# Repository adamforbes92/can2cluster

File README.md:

# Can2Cluster

**Get one ready-built:** [Can2Cluster at Forbes Automotive](https://forbes-automotive.com/products/can2cluster?utm_source=github&utm_medium=readme&utm_campaign=can2cluster) · Pair it with a [SpeedPulser](https://forbes-automotive.com/products/speedpulser?utm_source=github&utm_medium=readme&utm_campaign=can2cluster) for cable speedos · Not sure which board you need? See the [speedo, tacho & cluster comparison](https://forbes-automotive.com/collections/speedo-tacho-cluster?utm_source=github&utm_medium=readme&utm_campaign=can2cluster).
Can2Cluster takes CAN messages and turns them into the analogue signals older instrument clusters expect: RPM, speed, Engine Management Light (EML), Electronic Pedal Control light (EPC), reverse and a coolant gauge. It is built around VAG CAN messages (PQ and MQB), with Ford, Emerald and Renault ECUs added too, and runs on an ESP32 DevKit board or the newer ESP32-S3 board from the same code.

DSG gearboxes are supported: speed can be worked out from the current gear and RPM, or read over TP2.0 / UDS. The DSG paddle inputs can shift an MQB or PQ gearbox over CAN, or, on a PQ car with an MK4 cruise stalk, the same inputs can carry the cruise stalk to the ECU.

If no speed is available (from hall or CAN), an optional GPS module (like the Neo6M) can provide it, and the speed can be broadcast on CAN for other modules. GPS modules need to see the sky; depending on where the unit is fitted, an external aerial may be needed (standard SMA connector).

Everything is set up from a web page on the unit's own WiFi, so no code editing is needed, and it shows live feedback on what's coming in.

> [!NOTE]
> The pin-out differs between the Version 1 and Version 2 PCBs, although functionality is the same. Confirm pin-outs using the 'Module Pinout' table.

This can be expanded to support other marques and is actively encouraged. Other users are using the DSG support and the EML/EPC outputs for shift lights and other features.

### Purchase
If you want to purchase an assembled Can2Cluster, you can do so here: [Can2Cluster - Forbes Automotive](https://forbes-automotive.com/products/can2cluster)

## Features
| Feature | What it does |
|---|---|
| RPM output | Square wave or high-voltage 'coil type' (MK1/MK2) RPM, from CAN or a hall RPM input |
| Speed output | Square wave speed from hall, VR, ECU, ABS, DSG, TP2.0/UDS, GPS or a custom CAN ID |
| EML / EPC / Reverse | Warning lights and a 5A reverse output from CAN |
| Needle sweep | Sweeps both needles at power-up, as soon as the outputs are ready, up to a settable speedo dial top |
| Shift light | Flashes EML and/or EPC above a set RPM |
| DSG park | Shows Park on the EML or EPC light |
| DSG paddles | Paddle inputs sent to an MQB (0x3DD) or PQ (0x38A) gearbox |
| MK4 cruise stalk | The paddle and hall inputs read an MK4 cruise stalk and send it to a PQ ECU (0x38A) |
| PQ gateway frames | Optional 0x570 / 0x390 / 0x7D0 for a PQ engine and DSG with no gateway |
| Coolant gauge | Drives an MK2-style coolant gauge from the CAN coolant temperature, with a calibration builder |
| GPS + speed broadcast | GPS speed, and any speed put back onto CAN on an ID of your choosing |
| CAN analyzer | Every frame forwarded to SavvyCAN over WiFi or USB |
| OTA updates | Firmware and web page updates from GitHub or from files, no USB needed |

## IO
Can2Cluster uses an 18-pin MX23A18 connector and features the following IO:

#### IO List
| Type | Signal | Notes |
|-----|--------|-------|
| Input | CAN (High & Low) | CANBUS |
| Input | DSG Paddle + / Cruise Main Switch | Ground to activate |
| Input | DSG Paddle - / Cruise SET | Ground to activate |
| Input | Hall Speed / Cruise RESUME | Pull-up/down options |
| Input | Hall RPM | Pull-down ONLY |
| Input | GPS | Neo6M or similar |
| Output | RPM (MK1/MK2) | High voltage 'coil type' |
| Output | RPM Square | Pull-down ONLY |
| Output | Speed Square | Pull-down ONLY |
| Output | EML & EPC | Pull-down ONLY |
| Output | Reverse | 5A high-side |

### Pinout
The MX23A18 connector pinout is:

| Pin | Signal | Notes |
|-----|--------|-------|
| 1 | Vign | 12V Ignition |
| 2 | Ground | Chassis ground |
| 3 | Chassis CAN Low | to Chassis/ECU side |
| 4 | Chassis CAN High | to Chassis/ECU side |
| 5 | Speed | Speed output; pull-down |
| 6 | RPM | RPM output; pull-down |
| 7 | EML | Engine Management Light; pull-down |
| 8 | EPC | Electronic Pedal Control Light; pull-down |
| 9 | Reverse | 12v high-side reverse output; 5A max |
| 10 | Paddle Up / Cruise Main | DSG paddle +, or the MK4 cruise main switch in cruise stalk mode; ground to activate |
| 11 | Paddle Down / Cruise SET | DSG paddle -, or cruise SET in cruise stalk mode; ground to activate |
| 12 | Hall Speed / Cruise RESUME | Hall speed sensor, or cruise RESUME in cruise stalk mode; optional pull-up/down |
| 13 | N/A | Not used |
| 14 | N/A | Not used |
| 15 | N/A | Not used |
| 16 | N/A | Not used (S3 board: coolant gauge output) |
| 17 | N/A | Not used |
| 18 | RPM | High voltage coil pulse; MK1/MK2 etc |

> [!NOTE]
> **Legacy clusters & needle jitter:** on some older clusters the coil-style RPM output can induce a little jitter in the hall inputs due to poor grounding. Fitting a **~500 Ω resistor in series** with the RPM output largely reduces this.

## Setup
Purchased modules come pre-loaded with the most recent firmware; check back here for updates.

1. Connect the module as per the wiring diagram.
2. Power up. WiFi is available straight away and stays on while any client is connected; once the last one disconnects, the radio turns off after 1 minute to save power (see Power Management below).
3. Connect to the device and browse to **192.168.1.1**.
4. Configure the device to suit: needle sweep and dial top, RPM type, speed source, shift light, input mode.
5. Use the **Diagnostics** tab to confirm incoming data.

### WiFi Setup
Connect to the **`Can2Cluster`** access point (open network, no password) and browse to **192.168.1.1** or **c2c.local**. The web page uses Forbes Automotive's shared dark theme, the same look as OpenHaldex, SpeedPulser, SpeedPulserPro, can2rpm, the MQB Steering Wheel Controller and AirLift Controller. Current firmware version: **4.03**.

The web page has five tabs:
- **Dashboard**: final RPM and speed (as numbers or dials) and the status pills.
- **Configuration**: needle sweep, shift light, cluster output (coil RPM, MPH), DSG park, input mode (paddles or MK4 cruise stalk), PQ gateway frames and DSG paddle output.
- **Advanced**: speed broadcast, GPS update rate, CAN analyzer, speed and RPM sources, custom CAN input, DSG speed calculation and the coolant gauge.
- **Diagnostics**: board details, every input side by side, and the output tests.
- **OTA**: updates from GitHub or from files, and Home WiFi (bridge mode).

*Dashboard with the final RPM/speed as dial gauges and the status pills; needle sweep, shift light, cluster output and DSG park on the Configuration tab; speed and RPM source selection under Advanced. Choosing **DSG** as the speed source reveals the gear-ratio calculator (speed = RPM × tyre circumference ÷ gear ratio × final drive).*

**Status indicators:** CAN health, GPS and output (EML/EPC/Reverse) status are shown as coloured pills:

| Colour | Meaning |
|---|---|
| Green | Healthy / active: CAN bus is healthy, GPS has a satellite lock, or the output reflects a real vehicle CAN signal |
| Red | Unhealthy / not available: CAN bus unhealthy, or no GPS module fitted/connected |
| Orange | A caveat, not a failure: GPS module connected but no satellite fix yet ("Connected (no sats)"), or an EML/EPC/Reverse output **forced on by the test/diagnostic mode** rather than a real vehicle signal |

### Needle Sweep
At power-up both needles sweep to the top of the dial and back. The sweep starts as soon as the output pins are set up, a fraction of a second after power-on, and runs on its own while the rest of the unit starts up (GPS search, CAN, WiFi), so there's no wait before it.

**Speedo Dial Top** sets how far the speed needle goes: set it to the highest number on the speedo (60 to 400, km/h or mph to match the cluster). Up to V4.01 the sweep always stopped at 200. **Sweep Speed**, **RPM Step** and **Speed Step** set how long the sweep takes (higher = slower); **Test Needle Sweep** runs one from the page.

## DSG Paddles
Pulling the DSG Paddle +/- inputs puts a paddle request on the CAN bus, whatever the speed source. The **DSG Paddle Output** drop-down picks the frame: **MQB** sends Gateway_74 (`0x3DD`), the frame an MQB gearbox reads its steering-wheel paddles from; **PQ** sends the GRA frame (`0x38A`); **PQ + MQB** sends both; **Off** sends nothing. Pick the one that matches the gearbox: a PQ gearbox only reads `0x38A` and an MQB one only `0x3DD`, so the wrong choice does nothing. Each pull sends **one clean tip**: a short pulse on the paddle's rising edge, then the bit is released, with a brief lock-out before the next shift. That is how the gearbox actually takes a tip (edge-triggered, one shift per press, with a minimum gap between shifts) - worked out by reverse-engineering the DSG firmware, write-ups in [Documents/dsg_re/](Documents/dsg_re/). Holding a paddle gives exactly one shift. If a real gateway is already sending that frame, Can2Cluster stays quiet on it. The MQB gear selector's own frame (`0x0AF`) is only read, never sent: the gearbox checks the lever with a question/answer and a message counter, so it can't be imitated while the real lever is fitted. The card also shows the lever position, the gearbox's tip mode, gear and warning level live, and has **Test Paddle +/-** buttons. The full log analysis is in [MQB_PADDLES.md](MQB_PADDLES.md).

## MK4 Cruise Stalk
For a PQ engine in a car with the MK4 cruise stalk. **Input Mode** (Configuration tab) picks what connector pins 10, 11 and 12 are used for:

| Pin | DSG Paddles (default) | MK4 Cruise Stalk |
|---|---|---|
| 10 | Paddle + | Main switch |
| 11 | Paddle - | SET |
| 12 | Hall speed | RESUME |

In cruise stalk mode each input is on when grounded, and the stalk goes to the ECU in the PQ cruise frame GRA (`0x38A`) every 20 ms: main switch, SET and RESUME, plus "cancel" for a moment when the main switch is switched off. The paddle bits in that frame are always 0, so the stalk can never shift the gearbox, and no paddle frames are sent. Hall speed isn't available in this mode (pin 12 is RESUME), so pick another speed source. The card shows each stalk input and what's being sent live; check every stalk position there before driving. Cruise also has to be enabled in the ECU coding, and the ECU must see both brake switches.

> [!WARNING]
> Match the setting to the wiring. In paddle mode, grounding pin 10 or 11 shifts the gearbox, so never select DSG Paddles while the cruise stalk is wired to those pins. The page asks for confirmation before switching.

**PQ Gateway Frames** (off by default) is for a PQ35/46 engine and DSG in a car without the right gateway. It sends the frames a gateway would normally send, so the ECU and DSG stop logging them as missing: `0x570` (ignition on / engine running and the battery voltage) and `0x390` (reverse gear) every 100 ms, and `0x7D0` every 500 ms with the mileage read from the cluster (`0x520`). Each frame stops by itself while another module sends it, so leave it off on cars that have a gateway.

The cruise stalk and gateway frames were first built by a customer for their own car (an MK4 build of 4.01) and are now part of the standard firmware. Their settings carry across when updating from that build.

## Adding CAN Functionality
Users wishing to add CAN functionality are encouraged to push commits to the project. Incoming CAN messages are handled in `onBodyRX()` (`can2cluster_can.cpp`) and the outputs follow automatically. You'll need to know the CAN ID and bytes you want to process and which variables to put them in.

Two things in the web page help here. **CAN Analyzer** (Advanced tab) forwards every received frame to [SavvyCAN](https://www.savvycan.com/) over WiFi (GVRET, `192.168.1.1:23`) or over the USB serial port, so you can find the ID and bytes you're after. And for a speed signal on a non-standard ID, **Custom CAN Input** (choose *Custom* as the speed source) lets you enter the CAN ID, byte positions, byte order, scale and offset without touching the code:

For example (in `can2cluster_can.cpp`, `onBodyRX()`):
```
  case emeraldECU1_ID:
    vehicleRPMCAN = ((frame.data[0] << 8) | frame.data[1]); // this is RPM
    break;

  case emeraldECU2_ID:
    calcSpeed = ((frame.data[2] << 8) | frame.data[3]) * (2.25 / 256); // this is speed
    break;
```
The above checks for a CAN message from `0x1000` or `0x1001` (Emerald ECU 1 & 2) and puts the data into the matching variables.

## Adding GPS
GPS can be added later; the boards are already socketed for it. The 4-pin JST XH connector provides 3.3V, RX, TX and ground.

Once fitted, pick **GPS** as the speed source on the Advanced tab. The same tab sets the receiver's **update rate** and, if another module on the bus needs the speed, **Broadcast Speed** puts it onto CAN on an ID, byte layout and scale of your choosing (shown above).

## Hall & RPM Input Parsing
When speed or RPM comes from the hall/VR/pulse inputs (rather than CAN), the frequency is measured over a **window** rather than from a single edge-to-edge period. Each interrupt adds up the edge intervals and a count, and the task averages them once per loop (frequency = intervals ÷ summed interval time), which gives a true average over that window.

This matters because a single-period reading turns tone-wheel / tooth-spacing jitter straight into a jumpy needle. Pulses closer together than ~3 ms (> 333 Hz) are rejected as electrical noise, so ignition-coil interference on the input can't be mistaken for a real speed or RPM. **Max Hall / VR Sensor Frequency** is the sensor's frequency at 200 km/h; **Cluster Frequency Limit** and **Cluster RPM Limit** set the RPM scale.

Every input the module can see is listed side by side on the **Diagnostics** tab, so it's obvious which sources are live before choosing one, and the output tests drive the cluster directly from the page:

*Diagnostics: every speed and RPM source side by side; slider-driven speed and RPM output tests (the speed test goes up to the speedo dial top), the EML / EPC / reverse output tests and the diagnostic (forced-output) mode that shows as orange pills on the dashboard; and the board details. On the S3 board this card also shows the coolant DAC (MCP4725), the board ID, CAN termination, output pull-ups and the speed input bias.*

## Coolant Gauge Output
The MK2-style coolant temperature gauge can be driven from the CAN coolant temperature. On the DevKit board it uses one of the ULN2003 outputs (EML or EPC; selecting one takes that pin away from the shift light / DSG park). On the S3 board it has its own output (connector pin 16) and follows the calibration curve. At or above the **warning temperature** the gauge is pegged and the cluster warning light is triggered.

Because every gauge is different, the **Calibration Builder** lets you drive the needle directly: enable calibration mode, jog the duty until the needle sits on a known mark, pick that temperature and **Capture**. The stored points are drawn as a curve and interpolated at runtime.

## Jumpers
To keep functionality, there are a variety of jumpers on the board which can be added/removed to suit the chassis.

### R-Term
The jumper marked 'r-term' is the terminating resistor for the CANBUS network. If there are no other CAN devices on the network (this is the only one), the jumper should stay. If there are other devices on the network, it can be removed.

### SpeedPulser
Selects pull-up or pull-down for a hall sensor, with the central pin being the hall sensor itself. Typically VAG ones are 'pull-up'. For the MK4 cruise stalk's RESUME button on pin 12, use pull-up.

### 12v Pullup
Used to configure outputs if the cluster does not have internal pull-ups.

## Over-the-Air Updates
Everything happens on the **OTA** tab; USB is only needed for the very first install, or if the web interface is ever lost.

- **Update from GitHub**: press **Check for updates**. The page reads the release list from [`adamforbes92/can2cluster`](https://github.com/adamforbes92/can2cluster) (`Releases/releases.json` plus the `V…` folders), shows *Installed* vs. *Latest* (older and beta releases sit behind a tick-box, for rolling back), then installs the selected version in six tracked steps: download and flash the web UI, verify it, download and flash the firmware, reboot. Each board is only offered its own firmware. The browser needs internet *while it can still reach the controller*: join the controller to your router in the **Home WiFi (Bridge Mode)** card, put the phone on the same network and open the address the card shows (`http://c2c.local/` works there too). On the controller's own access point alone most phones drop mobile data.
- **Home WiFi (Bridge Mode)**: the controller joins a home or garage network as a station alongside its own access point. Scan or type the network name, save, and once it shows *Connected* the controller is reachable from that network as well. It tries hard for 20 s after boot, then once every 5 minutes, so a saved network can't disturb the access point when the car is parked away from home.
- **Update from Files**: no internet needed. Download `littlefs.bin` and `firmware.bin` from the newest `Releases/V…/` folder and upload them here, **Filesystem** (web UI) first, then **Firmware**. The device reboots after the firmware.

Every upload is size-checked, and a filesystem image is verified by mounting it before the device reports success; a failed filesystem upload is wiped rather than left half-written. If the web interface is ever missing (a filesystem update that stopped part-way), the controller serves a **recovery page** at its address with the same two uploads and partition diagnostics, so it is never a USB job. Web files are served `no-cache`, so a new UI is never hidden behind a stale copy in the phone's browser.

## Power Management
The firmware includes a reduced-power module that saves current once no clients are connected to the WiFi access point. This directly reduces heat from the on-board linear regulator, which turns `(Vin − Vout) × current` into heat, so every milliamp saved is less heat.

**1 minute after the last client disconnects:**
- WiFi radio off: the single biggest saving (~80–120 mA average)
- CPU scaled from 240 MHz to 80 MHz

Bluetooth is released at boot (frees ~60 KB RAM) and the onboard LED is switched off. Everything comes back the moment a client reconnects, and a power-cycle (ignition off/on) also brings WiFi back.

## PCB Design
The PCB has been designed in EasyEDA and is in the 'PCB' folder.

## PCB Principles
The DevKit board is based around an ESP32 with an external CAN chip (SN65HVD230) and an optional termination resistor (if there are no other CAN devices on the network).

The outputs are driven through a ULN2003A (a 200mA 7-channel Darlington array), socketed so it can be swapped if damaged. It also triggers the high-side 5A MOSFET (typically for the reverse light).

GPS is read from a Neo6M module on a hardware serial port. It comes with an aerial, although a cabled external aerial may be needed; the connector is a standard SMA ("sma gps antenna" on Google finds them).

The S3 board uses an ESP32-S3-WROOM-1-N16R8 with native USB, a TCAN1044 CAN transceiver with switchable termination, a TPL7407 output driver, switchable 12V pull-ups and a dedicated coolant gauge output (MCP4725 DAC driving a current sink).

## Version History
- **4.03**: DSG paddles reworked and the MQB DSG speed read fixed, after reverse-engineering the gearbox firmware (write-ups in [Documents/dsg_re/](Documents/dsg_re/)). Each pull now sends one clean tip (a short pulse on the rising edge, then released, with a lock-out before the next) instead of holding the bit, which stops the odd double gear-jump and the need to press twice. MQB DSG speed now read over UDS as DID `0x100A` (km/h = raw/10) on `0x7E1/0x7E9`, replacing a wrong placeholder; PQ DSG speed (TP2.0, raw/3) confirmed correct and unchanged.
- **4.02**: MK4 cruise stalk input mode (pins 10/11/12 to a PQ ECU on 0x38A) and optional PQ gateway frames (0x570 / 0x390 / 0x7D0), both from a customer's MK4 build; needle sweep starts straight away instead of after the GPS search; settable Speedo Dial Top for the sweep (was fixed at 200).
- **4.01**: MQB paddles rebuilt from a full log review (Gateway_74 0x3DD, held for as long as the paddle), selector emulation removed, paddle readout and test buttons on the web page.
- **4.00**: one codebase for the DevKit and the new ESP32-S3 board (dedicated coolant gauge output).
- **3.24**: OTA overhaul (Update from GitHub, Home WiFi bridge mode, recovery page); speed/RPM outputs moved to hardware timers.
- **3.23**: shared Forbes Automotive web theme.
- **3.20 - 3.22**: MQB support, coolant gauge output, aftermarket speed input, Renault Megane RPM, MQB paddles.
- **3.10**: power management (WiFi off when idle).
- **3.00 - 3.02**: OTA, GPS rework, MPH clusters, SavvyCAN analyzer.
- **2.00 - 2.01**: TP2.0 / UDS DSG speed, PlatformIO port, GPS update rate.

The full history is in `include/can2cluster_ver.h`.

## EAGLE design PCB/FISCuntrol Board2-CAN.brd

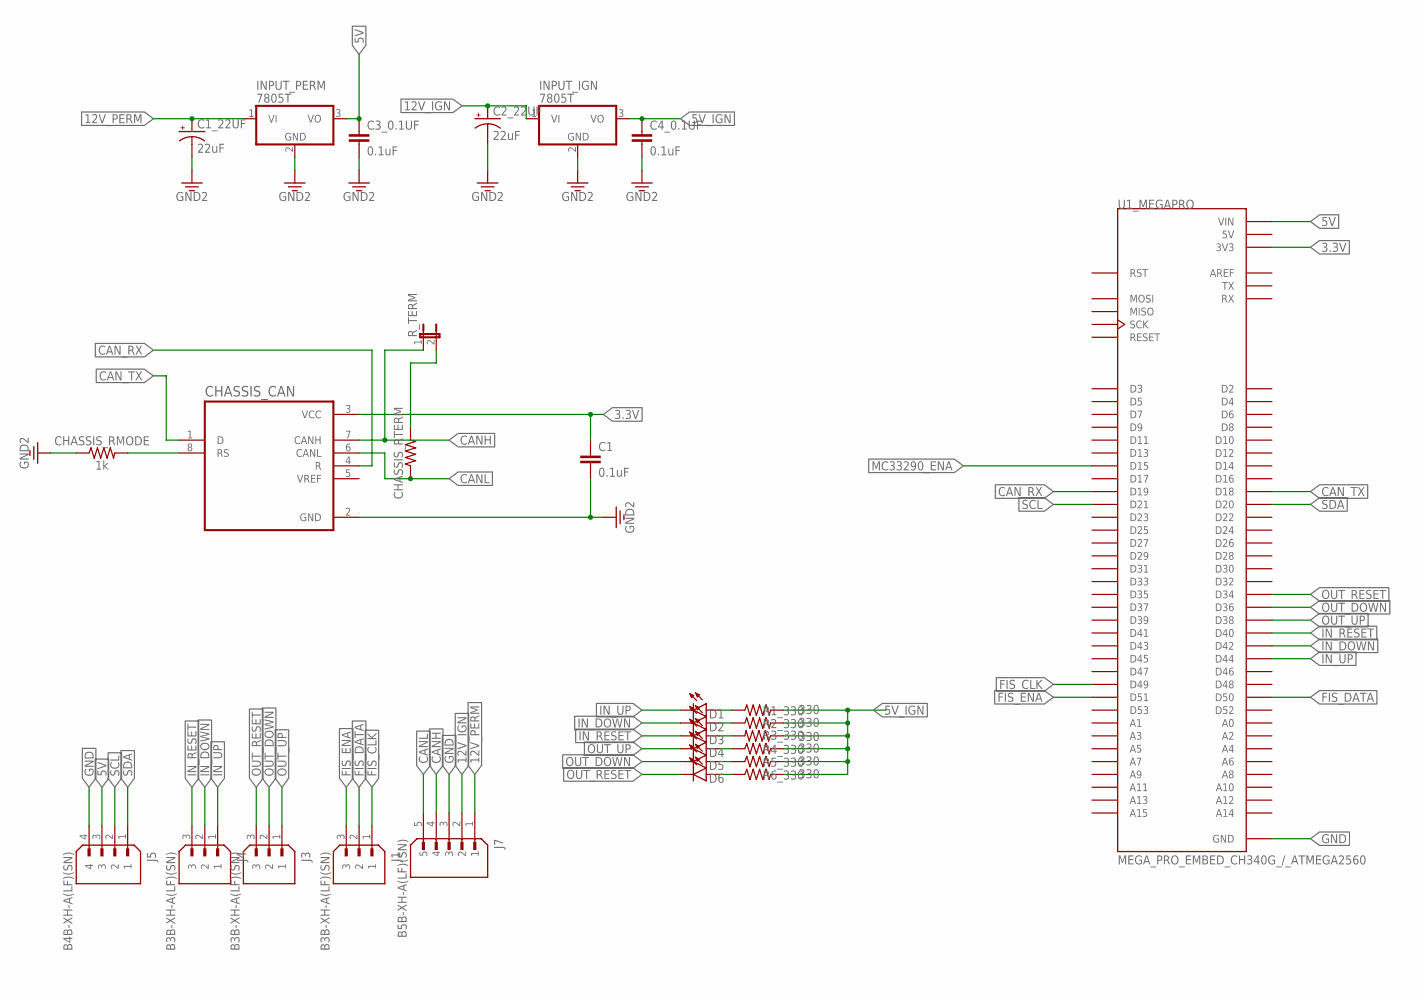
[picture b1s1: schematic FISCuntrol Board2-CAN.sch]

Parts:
C1: 0.1uF; 0402
C1_22UF, C2_22UF: 22uF; PANASONIC_C
C3_0.1UF, C4_0.1UF: 0.1uF; 0603
CHASSIS_CAN: SN65HVD230DR; SOIC127P599X175-8N
CHASSIS_RMODE: 1k; 0603
CHASSIS_RTERM: AXIAL-0.3
D1, D2, D3, D4, D5, D6: LED3MM; LED_3MM
INPUT_IGN: 7805T; TO220H
INPUT_PERM: 7805T; TO220H
J1, J3, J4: B3B-XH-A(LF)(SN); JST_B3B-XH-A(LF)(SN)
J5: B4B-XH-A(LF)(SN); JST_B4B-XH-A(LF)(SN)
J7: B5B-XH-A(LF)(SN); JST_B5B-XH-A(LF)(SN)
R1_330, R2_330, R3_330, R4_330, R5_330, R6_330: 330; AXIAL-0.3
R_TERM: JP1E; JP1
U1_MEGAPRO: MEGA_PRO_EMBED_CH340G_/_ATMEGA2560; MODULE_MEGA_PRO_EMBED_CH340G_/_ATMEGA2560

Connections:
3.3V: C1.1, CHASSIS_CAN.3 (VCC), U1_MEGAPRO.3V3_1 (3V3), U1_MEGAPRO.3V3_2 (3V3)
5V: C3_0.1UF.1, INPUT_PERM.3 (VO), J5.3, U1_MEGAPRO.5V_1 (5V), U1_MEGAPRO.5V_2 (5V), U1_MEGAPRO.5V_3 (5V), U1_MEGAPRO.VIN_1 (VIN), U1_MEGAPRO.VIN_2 (VIN)
5V_IGN: C4_0.1UF.1, INPUT_IGN.3 (VO), R1_330.P$2 (2), R2_330.P$2 (2), R3_330.P$1 (1), R4_330.P$2 (2), R5_330.P$2 (2), R6_330.P$2 (2)
12V_IGN: C2_22UF.+, INPUT_IGN.1 (VI), J7.2
12V_PERM: C1_22UF.+, INPUT_PERM.1 (VI), J7.1
CANH: CHASSIS_CAN.7 (CANH), J7.4, R_TERM.1
CANL: CHASSIS_CAN.6 (CANL), CHASSIS_RTERM.P$1 (1), J7.5
CAN_RX: CHASSIS_CAN.4 (R), U1_MEGAPRO.D19
CAN_TX: CHASSIS_CAN.1 (D), U1_MEGAPRO.D18
FIS_CLK: J1.1, U1_MEGAPRO.D49
FIS_DATA: J1.2, U1_MEGAPRO.D50
FIS_ENA: J1.3, U1_MEGAPRO.D51
GND: C1.2, C1_22UF.-, C2_22UF.-, C3_0.1UF.2, C4_0.1UF.2, CHASSIS_CAN.2 (GND), CHASSIS_RMODE.1, INPUT_IGN.2 (GND), INPUT_PERM.2 (GND), J5.4, J7.3, U1_MEGAPRO.GND_1 (GND), U1_MEGAPRO.GND_2 (GND), U1_MEGAPRO.GND_3 (GND)
IN_DOWN: D2.K (C), J4.2, U1_MEGAPRO.D42
IN_RESET: D3.K (C), J4.3, U1_MEGAPRO.D40
IN_UP: D1.K (C), J4.1, U1_MEGAPRO.D44
MC33290_ENA: U1_MEGAPRO.D15
unnamed: D1.A, R1_330.P$1 (1)
unnamed: D5.A, R5_330.P$1 (1)
unnamed: D2.A, R2_330.P$1 (1)
unnamed: D3.A, R3_330.P$2 (2)
unnamed: D6.A, R6_330.P$1 (1)
unnamed: D4.A, R4_330.P$1 (1)
unnamed: CHASSIS_CAN.8 (RS), CHASSIS_RMODE.2
unnamed: CHASSIS_RTERM.P$2 (2), R_TERM.2
OUT_DOWN: D5.K (C), J3.2, U1_MEGAPRO.D36
OUT_RESET: D6.K (C), J3.3, U1_MEGAPRO.D34
OUT_UP: D4.K (C), J3.1, U1_MEGAPRO.D38
SCL: J5.2, U1_MEGAPRO.D21
SDA: J5.1, U1_MEGAPRO.D20

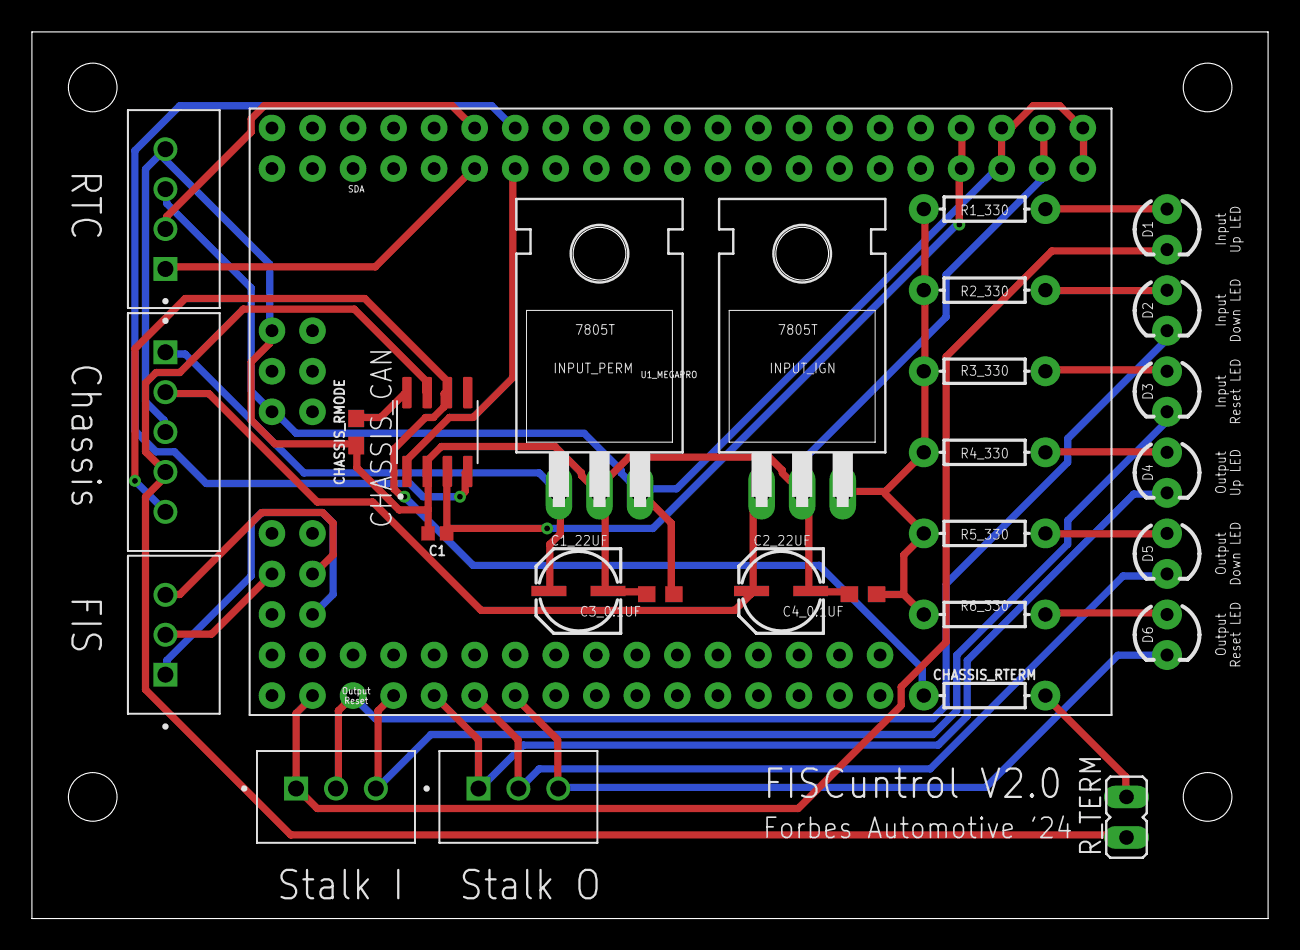
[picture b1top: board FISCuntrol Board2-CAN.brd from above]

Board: 2 copper layers, 77.5 x 55.5 mm, 29 parts (0 on the bottom side), 29 nets.

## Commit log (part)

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2024-10-25 V1.0
    First version, to be tested(!)
2025-01-17 V1.1
    Revised, confirmed working.
2025-01-17 V1.02
    Gerbers ordered
2025-01-20 PCBs
2025-01-26 V1.04 - without ABS
    Added DSG support without ABS
2025-01-26 V1.05
    Added upshift inputs
2025-01-27 V1.05
    Hanging check, beta
2025-01-27 V1.05
    Rewrite
2025-01-29 V1.05
    Update
2025-02-12 Installation Guide
    Installation Guide
2025-03-01 V1.03
    Revised.
2025-03-02 V1.06
    Slowed down RPM for shifting
2025-03-02 V1.06
2025-03-02 V.1.06
2025-03-27 V1.07
    Calibrated PWM motor
2025-03-27 V1.08
    Revised buttons
2025-05-18 V1.06
    Added Emerald
2025-07-24 Enclosure
    Added
2025-08-14 Module Pinouts
    Module pinouts
2025-08-17 V1.11
    Refresh
2025-09-02 V1.10
    Paddle revision
2025-09-02 V1.08 - DSG Reverse
    V1.08 - added DSG specifics
2025-09-04 Added enclosures
2025-09-07 V1.10 - Drop Down for Input Type
    Added drop-downs & an overall cleanup
2025-09-15 V1.11
    Added Ford details
2025-09-22 No serial comms
    Turned off to speed up
2025-09-23 Update Readme.
2025-10-10 V1.11
    Re-upload/confirm.
2025-10-10 V1.12
    Added MPH conversion
2025-10-12 Update readme.md
    Update readme.md
2025-10-26 V1.13
    V1.13 - added DSG Up/Down paddles & DSG gear logging
2025-10-30 V1.14
    V1.14 - changed button library to ESP32 Interrupt Button to make paddles faster
2025-10-30 V1.14
    Update, took off debug
2025-10-30 V1.14
    Added images
2025-10-30 V1.14
2025-10-31 Update can2cluster_can.ino
    Changed abs speed
2025-12-05 V1.14
    Moved to tasks; added test functionality
2025-12-05 Add purchase section to README
    Added purchase information for Can2Cluster.
2025-12-05 V1.17
    Revised needle sweep code and neatened code
2025-12-05 V1.17
    Corrected EEP last values
2026-01-29 Added board connector
2026-01-31 V1.16
    Added OTA, moved everything to tasks and added 'slow' response on WiFi to see paddles actually work
2026-01-31 Update Readme
    With WiFi screenshots
2026-02-01 update wifi
2026-02-01 updated wifi
2026-02-01 Update can2cluster.ino
    Moved WiFi north
2026-02-06 Speed update
2026-02-17 Latest, missed a var
2026-03-01 V1.18
    Added error on GPS wiring
2026-03-01 Readme update
2026-03-13 Releases
    added
2026-03-22 V2.00
    Release
2026-03-22 V2.00
2026-03-22 V2.00
    PlatformIO Port
2026-04-07 Pinout (Mini)
    Added Mini pinout
2026-04-11 V2.01
2026-05-02 V2.0
    Revised park lock.
2026-05-04 Custom CAN Speed
2026-05-29 V3.00
    Major GPS updates
2026-05-30 V3.00
    Added UDS/TP2.0, Speed/RPM Hall improvements, needle sweep
2026-06-14 V3.01
    Added SavvyCAN, diag testing.
2026-06-14 V3.01
    Added DSG, TP2.0, UDS, SavvyCAN and Diag.
2026-06-21 V3.02
    Moved GPS to Hardware Serial
2026-06-23 V3.10
    Added power management

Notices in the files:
parts and their libraries:
SparkFun-Capacitors: Licensing: Creative Commons ShareAlike 4.0 International - https://creativecommons.org/licenses/by-sa/4.0
